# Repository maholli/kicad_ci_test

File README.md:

# kicad_ci_test

## maholli

Test for Continuous Integration using KiCad.

This is an example of how to test and generate documentation for a KiCad project automatically every time you commit a change to the schematic and/or PCB.

In this example we use a [docker image](https://github.com/INTI-CMNB/kicad_auto) containing KiCad, [KiPlot](https://github.com/INTI-CMNB/kiplot) and all the supporting tools.

The [kicad_ci_test.kiplot.yaml](https://github.com/INTI-CMNB/kicad_ci_test/blob/master/kicad_ci_test.kiplot.yaml) configures KiPlot and says what's available.

The [.github/workflows/test1.yml](https://github.com/INTI-CMNB/kicad_ci_test/blob/master/.github/workflows/test1.yml) configures what GitHub makes.

In this file we:

* Instruct GitHub to run the tasks every time a change in the pertinent files is detected:

```
on:
  push:
    branches: [ master ]
    paths:
      - '**.sch'
      - '**.kicad_pcb'
  pull_request:
    branches: [ master ]
    paths:
      - '**.sch'
      - '**.kicad_pcb'
```

* Define actions for ERC, DRC, schematic documentation generation and PCB documentation generation.
* Each action takes the repo content as input using:

```
- uses: actions/checkout@v2
```

* The actions are executed by KiPlot and stored in the *Fabrication* directory

* The resulting files are stored as *artifacts* using:

```
 - name: Recuperar resultados
      uses: actions/upload-artifact@v1
      with:
        name: ERC_Output
        path: Fabrication
```

For more information about the GitHub configuration read the [Workflow syntax for GitHub Actions](https://help.github.com/en/actions/reference/workflow-syntax-for-github-actions) page.

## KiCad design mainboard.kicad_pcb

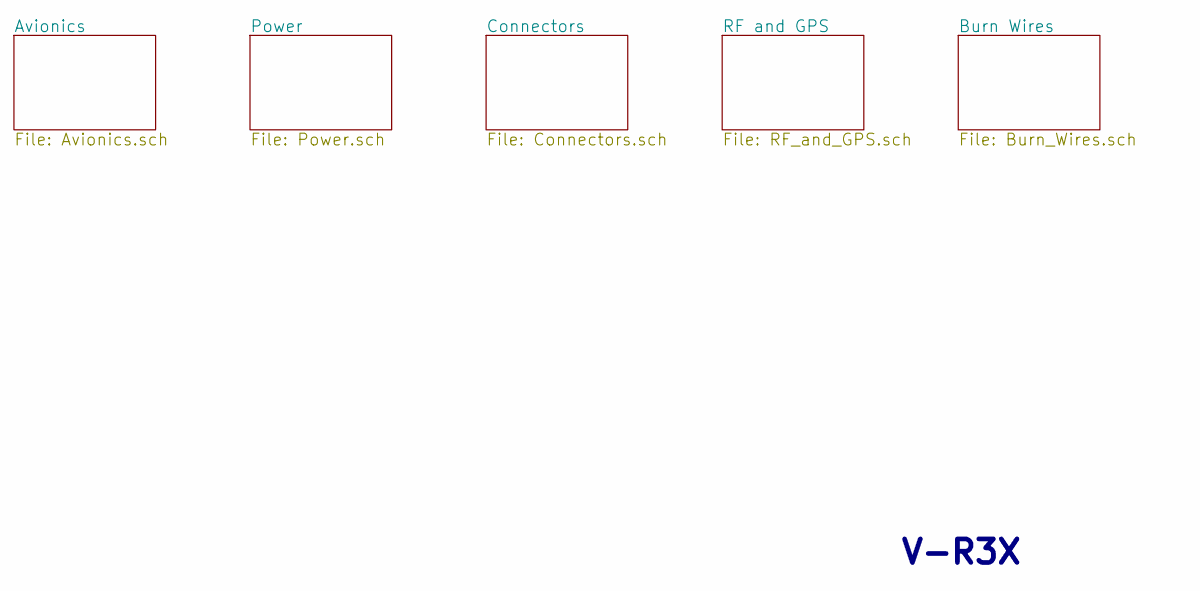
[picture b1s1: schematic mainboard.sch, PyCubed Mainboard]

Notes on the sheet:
V-R3X

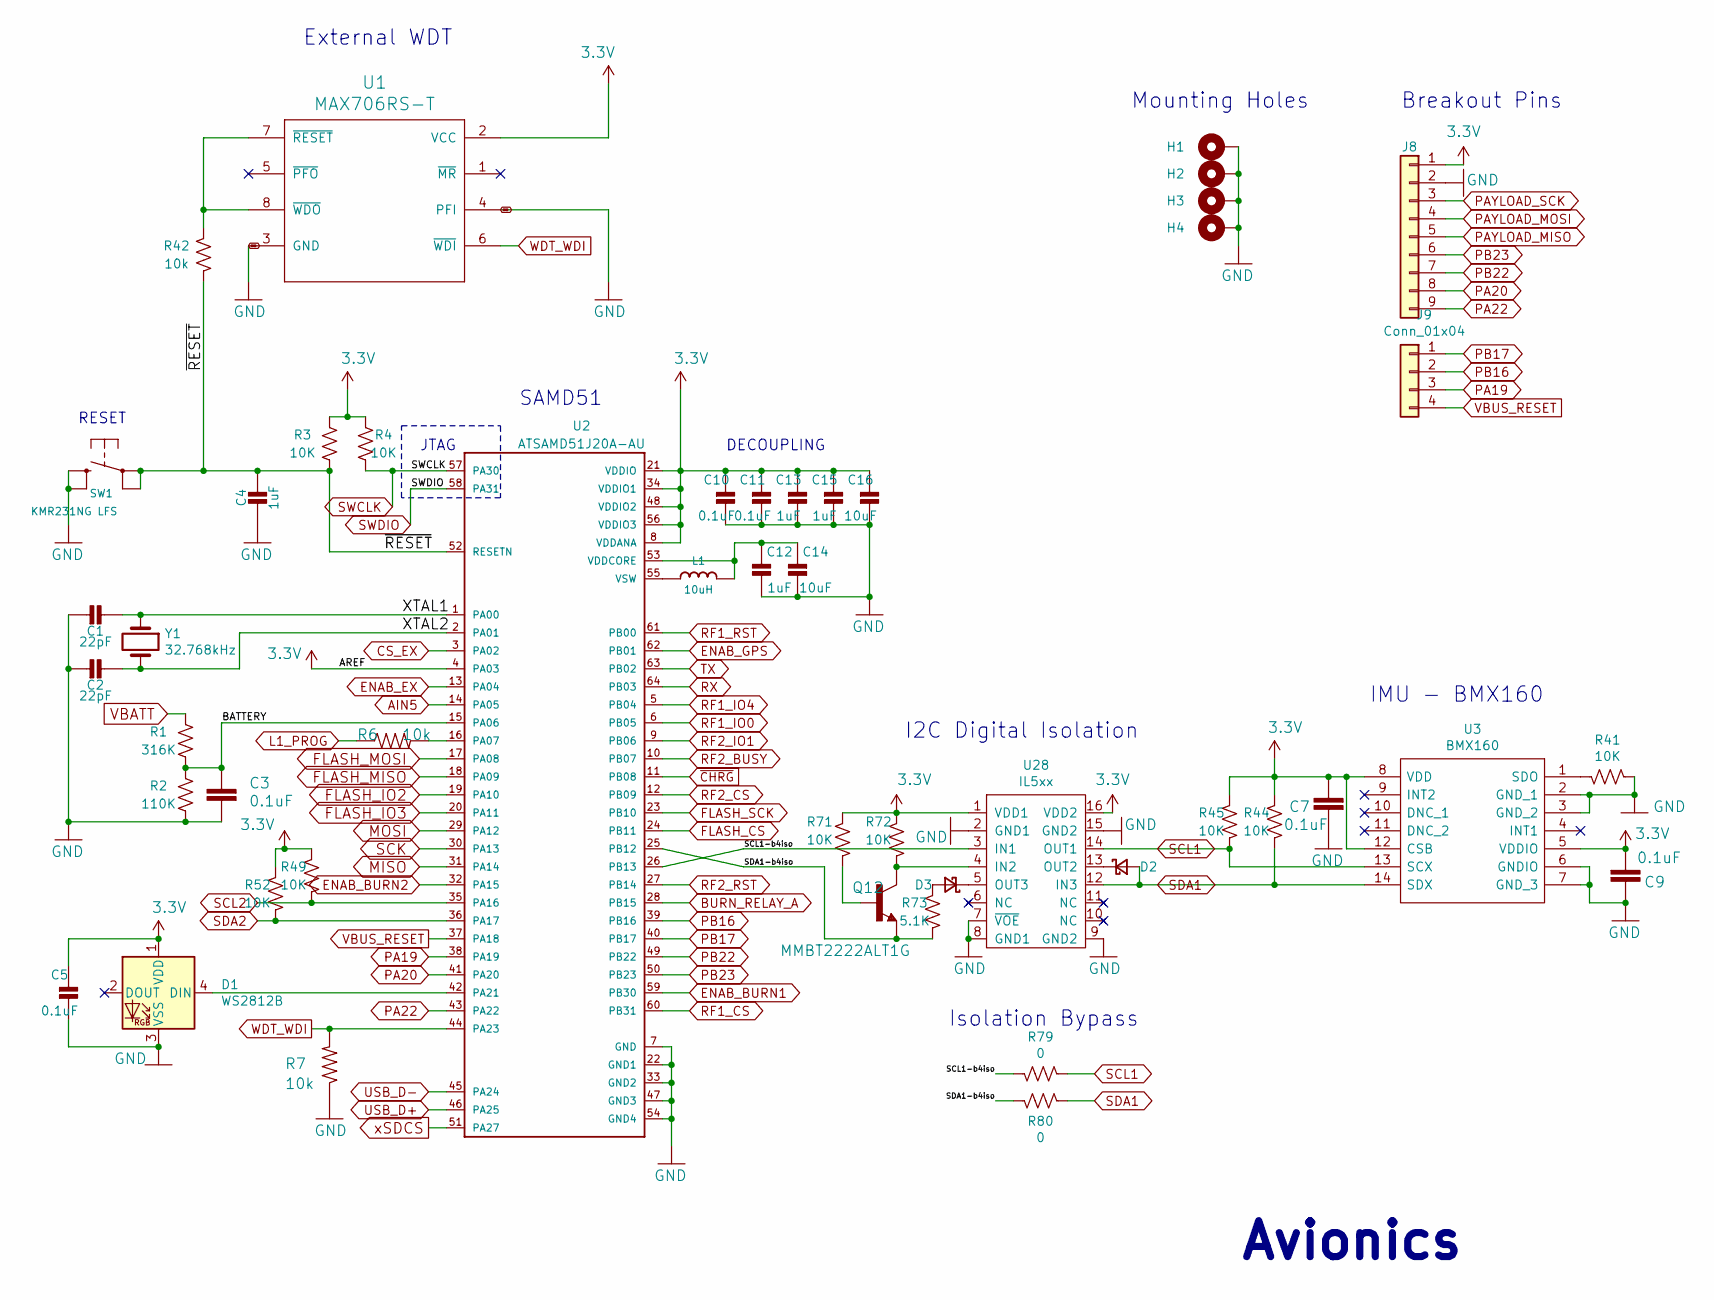
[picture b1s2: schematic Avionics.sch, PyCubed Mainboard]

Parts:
C1, C2: 22pF; C_0603_1608Metric
C3, C5, C7, C9, C10, C11: 0.1uF; C_0603_1608Metric
C4, C12, C13, C15: 1uF; C_0603_1608Metric
C14, C16: 10uF; C_0603_1608Metric
D1: WS2812B; LED_WS2812B_PLCC4_5.0x5.0mm_P3.2mm
D2, D3: RB550VAM; SOD-323HE
H1, H2, H3, H4: MountingHole_Pad; MountingHole_3.2mm_M3_DIN965_Pad
J8: Conn_01x09; PinHeader_1x09_P2.54mm_Vertical
J9: Conn_01x04; PinHeader_1x04_P2.54mm_Vertical
L1: 10uH; L_0805_2012Metric_Pad1.15x1.40mm_HandSolder
Q12: MMBT2222ALT1G; SOT23
R1: 316K; R_0603_1608Metric
R2: 110K; R_0603_1608Metric
R3, R4, R41, R44, R45, R49, R52, R71, R72: 10K; R_0603_1608Metric
R6, R7, R42: 10k; R_0603_1608Metric
R73: 5.1K; R_0603_1608Metric
R79, R80: 0; R_0603_1608Metric
SW1: KMR231NG LFS; BTN_KMR2_4.6X2.8
U1: MAX706RS-T; SO-8_3.9x4.9mm_P1.27mm
U2: ATSAMD51J20A-AU; QFP50P1200X1200X120-64N
U3: BMX160; Manufacturer_Part_Number BMX160; Mouser Part Number 262-BMX160
U28: IL5xx; SOIC-16_IL5xx
Y1: 32.768kHz; Crystal_SMD_3215-2Pin_3.2x1.5mm

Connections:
3.3V: C5.1, C7.1, C9.2, C10.1, C11.1, C13.1, C15.1, C16.1, D1.1 (VDD), J8.1, R3.1, R4.1, R44.1, R45.1, R49.1, R52.1, R71.2, R72.1, U1.2 (VCC), U2.4 (PA03), U2.8 (VDDANA), U2.21 (VDDIO), U2.34 (VDDIO1), U2.48 (VDDIO2), U2.56 (VDDIO3), U3.5 (VDDIO), U3.8 (VDD), U3.12 (CSB), U28.1 (VDD1), U28.16 (VDD2); also elsewhere on the board
/Avionics/BATTERY: C3.1, R1.2, R2.2, U2.15 (PA06)
/Avionics/SCL1-b4iso: R79.1, U2.26 (PB13), U28.3 (IN1)
/Avionics/SDA1-b4iso: Q12.2 (E), R73.2, R80.1, U2.25 (PB12)
/Avionics/XTAL1: C1.1, U2.1 (PA00), Y1.1
/Avionics/XTAL2: C2.1, U2.2 (PA01), Y1.2
/Avionics/~RESET: C4.2, R3.2, R42.1, SW1.A, SW1.A' (P1), U2.52 (RESETN)
AIN5: U2.14 (PA05); also elsewhere on the board
BURN_RELAY_A: U2.28 (PB15); also elsewhere on the board
CS_EX: U2.3 (PA02); also elsewhere on the board
ENAB_BURN1: U2.59 (PB30); also elsewhere on the board
ENAB_BURN2: U2.32 (PA15); also elsewhere on the board
ENAB_EX: U2.13 (PA04); also elsewhere on the board
ENAB_GPS: U2.62 (PB01); also elsewhere on the board
FLASH_CS: U2.24 (PB11); also elsewhere on the board
FLASH_IO2: U2.19 (PA10); also elsewhere on the board
FLASH_IO3: U2.20 (PA11); also elsewhere on the board
FLASH_MISO: U2.18 (PA09); also elsewhere on the board
FLASH_MOSI: U2.17 (PA08); also elsewhere on the board
FLASH_SCK: U2.23 (PB10); also elsewhere on the board
GND: C1.2, C2.2, C3.2, C4.1, C5.2, C7.2, C9.1, C10.2, C11.2, C12.1, C13.2, C14.2, C15.2, C16.2, D1.3 (VSS), H1.1, H2.1, H3.1, H4.1, J8.2, R2.1, R7.1, R41.1, SW1.B (S), SW1.B' (S1), U1.3 (GND), U1.4 (PFI), U2.7 (GND), U2.22 (GND1), U2.33 (GND2), U2.47 (GND3), U2.54 (GND4), U3.2 (GND_1), U3.3 (GND_2), U3.6 (GNDIO), U3.7 (GND_3), U28.2 (GND1), U28.7 (~VOE), U28.8 (GND1), U28.9 (GND2), U28.15 (GND2); also elsewhere on the board
L1_PROG: R6.1; also elsewhere on the board
MISO: U2.31 (PA14); also elsewhere on the board
MOSI: U2.29 (PA12); also elsewhere on the board
unnamed: C12.2, C14.1, L1.1, U2.53 (VDDCORE)
unnamed: D1.4 (DIN), U2.42 (PA21)
unnamed: D2.1 (K), U28.13 (OUT2)
unnamed: D3.1 (K), U28.5 (OUT3)
unnamed: D3.2 (A), R73.1
unnamed: L1.2, U2.55 (VSW)
unnamed: Q12.1 (B), R71.1
unnamed: Q12.3 (C), R72.2, U28.4 (IN2)
unnamed: R6.2, U2.16 (PA07)
unnamed: R41.2, U3.1 (SDO)
unnamed: R42.2, U1.7 (~RESET), U1.8 (~WDO)
PA19: J9.3, U2.38 (PA19); also elsewhere on the board
PA20: J8.8, U2.41 (PA20); also elsewhere on the board
PA22: J8.9, U2.43 (PA22); also elsewhere on the board
PAYLOAD_MISO: J8.5; also elsewhere on the board
PAYLOAD_MOSI: J8.4; also elsewhere on the board
PAYLOAD_SCK: J8.3; also elsewhere on the board
PB16: J9.2, U2.39 (PB16); also elsewhere on the board
PB17: J9.1, U2.40 (PB17); also elsewhere on the board
PB22: J8.7, U2.49 (PB22); also elsewhere on the board
PB23: J8.6, U2.50 (PB23); also elsewhere on the board
RF1_CS: U2.60 (PB31); also elsewhere on the board
RF1_IO0: U2.6 (PB05); also elsewhere on the board
RF1_IO4: U2.5 (PB04); also elsewhere on the board
RF1_RST: U2.61 (PB00); also elsewhere on the board
RF2_BUSY: U2.10 (PB07); also elsewhere on the board
RF2_CS: U2.12 (PB09); also elsewhere on the board
RF2_IO1: U2.9 (PB06); also elsewhere on the board
RF2_RST: U2.27 (PB14); also elsewhere on the board
RX: U2.64 (PB03); also elsewhere on the board
SCK: U2.30 (PA13); also elsewhere on the board
SCL1: R45.2, R79.2, U3.13 (SCX), U28.14 (OUT1); also elsewhere on the board
SCL2: R49.2, U2.35 (PA16); also elsewhere on the board
SDA1: D2.2 (A), R44.2, R80.2, U3.14 (SDX), U28.12 (IN3); also elsewhere on the board
SDA2: R52.2, U2.36 (PA17); also elsewhere on the board
SWCLK: R4.2, U2.57 (PA30); also elsewhere on the board
SWDIO: U2.58 (PA31); also elsewhere on the board
TX: U2.63 (PB02); also elsewhere on the board
USB_D+: U2.46 (PA25); also elsewhere on the board
USB_D-: U2.45 (PA24); also elsewhere on the board
VBATT: R1.1; also elsewhere on the board
VBUS_RESET: J9.4, U2.37 (PA18); also elsewhere on the board
WDT_WDI: R7.2, U1.6 (~WDI), U2.44 (PA23)
xSDCS: U2.51 (PA27); also elsewhere on the board
~CHRG: U2.11 (PB08); also elsewhere on the board

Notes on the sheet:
RESET
External WDT
JTAG
SAMD51
DECOUPLING
Mounting Holes
I2C Digital Isolation
Isolation Bypass
Avionics
Breakout Pins
IMU - BMX160

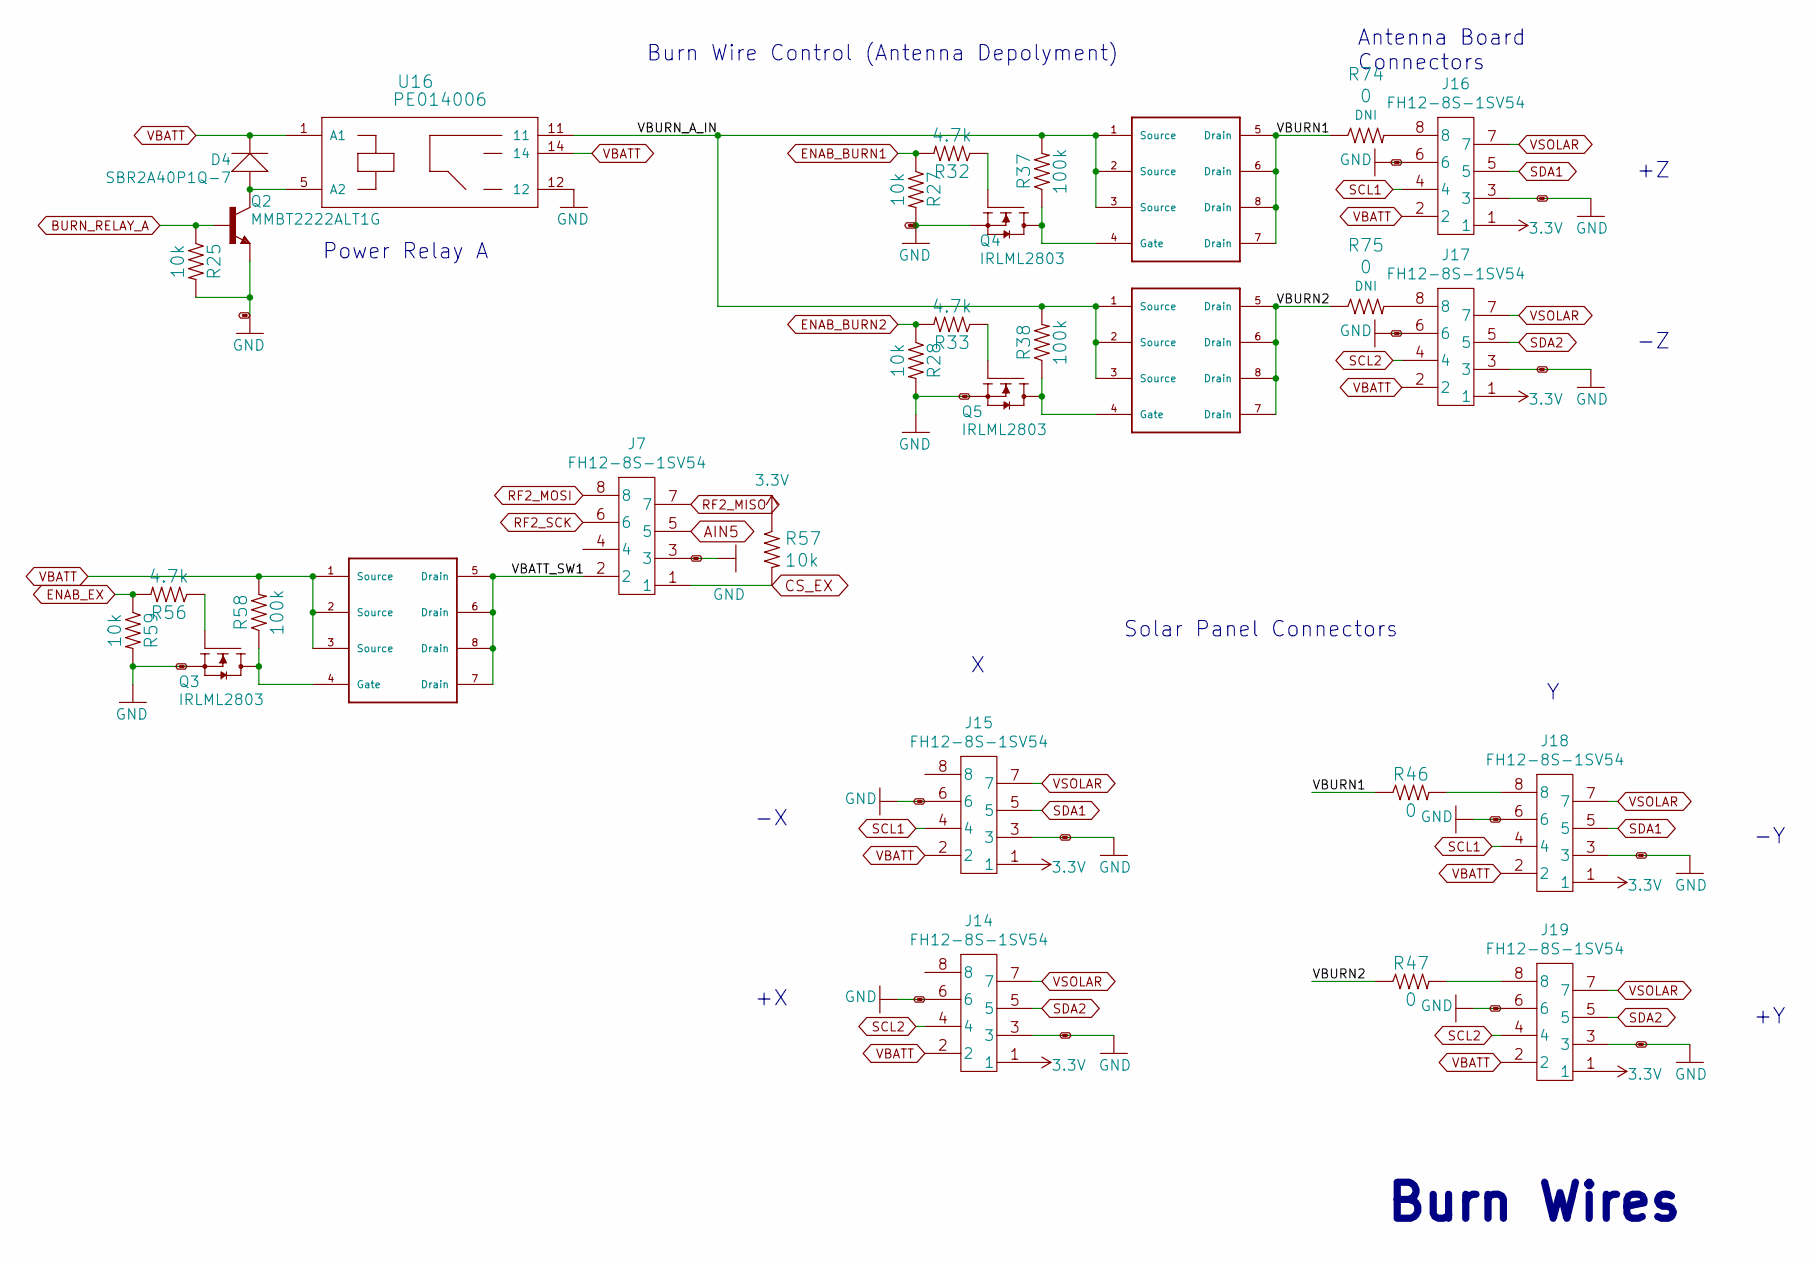
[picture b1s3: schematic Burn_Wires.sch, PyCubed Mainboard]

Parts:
D4: SBR2A40P1Q-7; PWRDI-123
J7, J14, J15, J16, J17, J18, J19: FH12-8S-1SV54; FH12-8S-1SV
Q2: MMBT2222ALT1G; SOT23
Q3, Q4, Q5: IRLML2803; SOT-23
R25, R27, R28, R57, R59: 10k; R_0603_1608Metric
R32, R33, R56: 4.7k; R_0603_1608Metric
R37, R38, R58: 100k; R_0603_1608Metric
R46, R47, R74, R75: 0; R_0603_1608Metric
U16: PE014006; RELAY5-PE_CO
U18, U19, U22: NDS8434

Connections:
3.3V: J14.1, J15.1, J16.1, J17.1, J18.1, J19.1, R57.1; also elsewhere on the board
/Burn Wires/VBATT_SW1: J7.2, U22.5 (Drain), U22.6 (Drain), U22.7 (Drain), U22.8 (Drain)
/Burn Wires/VBURN1: R46.1, R74.1, U18.5 (Drain), U18.6 (Drain), U18.7 (Drain), U18.8 (Drain)
/Burn Wires/VBURN2: R47.1, R75.1, U19.5 (Drain), U19.6 (Drain), U19.7 (Drain), U19.8 (Drain)
/Burn Wires/VBURN_A_IN: R37.2, R38.2, U16.11, U18.1 (Source), U18.2 (Source), U18.3 (Source), U19.1 (Source), U19.2 (Source), U19.3 (Source)
AIN5: J7.5; also elsewhere on the board
BURN_RELAY_A: Q2.1 (B), R25.1; also elsewhere on the board
CS_EX: J7.1, R57.2; also elsewhere on the board
ENAB_BURN1: R27.1, R32.2; also elsewhere on the board
ENAB_BURN2: R28.1, R33.2; also elsewhere on the board
ENAB_EX: R56.2, R59.1; also elsewhere on the board
GND: J7.3, J14.3, J14.6, J15.3, J15.6, J16.3, J16.6, J17.3, J17.6, J18.3, J18.6, J19.3, J19.6, Q2.2 (E), Q3.2 (S), Q4.2 (S), Q5.2 (S), R25.2, R27.2, R28.2, R59.2, U16.12; also elsewhere on the board
unnamed: D4.A, Q2.3 (C), U16.5 (A2)
unnamed: J16.8, R74.2
unnamed: J17.8, R75.2
unnamed: J18.8, R46.2
unnamed: J19.8, R47.2
unnamed: Q3.1 (G), R56.1
unnamed: Q3.3 (D), R58.1, U22.4 (Gate)
unnamed: Q4.1 (G), R32.1
unnamed: Q4.3 (D), R37.1, U18.4 (Gate)
unnamed: Q5.1 (G), R33.1
unnamed: Q5.3 (D), R38.1, U19.4 (Gate)
RF2_MISO: J7.7; also elsewhere on the board
RF2_MOSI: J7.8; also elsewhere on the board
RF2_SCK: J7.6; also elsewhere on the board
SCL1: J15.4, J16.4, J18.4; also elsewhere on the board
SCL2: J14.4, J17.4, J19.4; also elsewhere on the board
SDA1: J15.5, J16.5, J18.5; also elsewhere on the board
SDA2: J14.5, J17.5, J19.5; also elsewhere on the board
VBATT: D4.C, J14.2, J15.2, J16.2, J17.2, J18.2, J19.2, R58.2, U16.1 (A1), U16.14, U22.1 (Source), U22.2 (Source), U22.3 (Source); also elsewhere on the board
VSOLAR: J14.7, J15.7, J16.7, J17.7, J18.7, J19.7; also elsewhere on the board

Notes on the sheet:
Power Relay A
Burn Wire Control (Antenna Depolyment)
Solar Panel Connectors
Antenna Board Connectors
Burn Wires

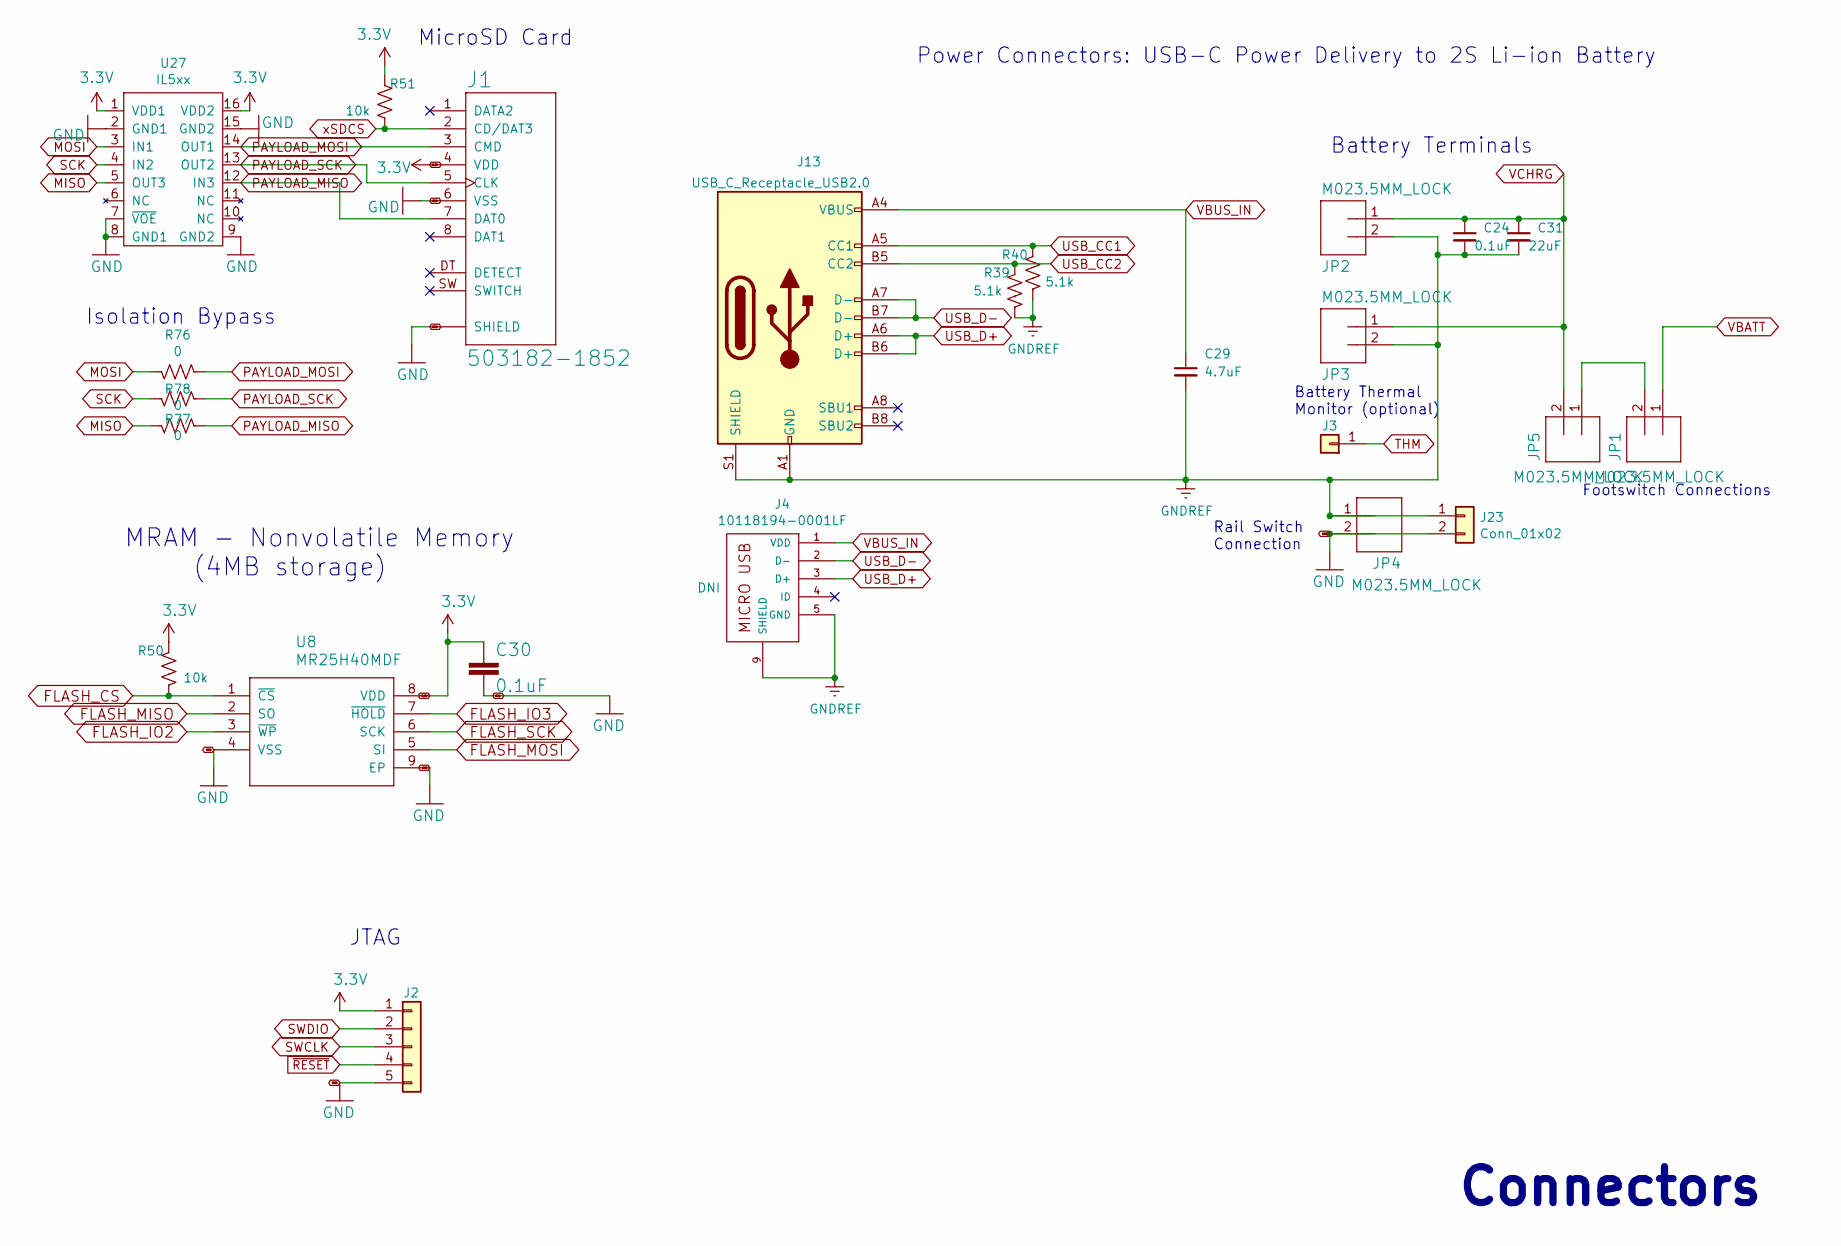
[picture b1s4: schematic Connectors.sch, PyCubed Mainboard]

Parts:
C24, C30: 0.1uF; C_0603_1608Metric
C29: 4.7uF; C_0603_1608Metric
C31: 22uF; C_0603_1608Metric
J1: 503182-1852; MOLEX_503182-1852
J2: Conn_01x05; PinHeader_1x05_P2.54mm_Vertical
J3: Conn_01x01; PinHeader_1x01_P2.54mm_Vertical
J4: 10118194-0001LF
J13: USB_C_Receptacle_USB2.0; USB_C_Receptacle_XKB_U262-161N-4BVC11
J23: Conn_01x02; PinHeader_1x02_P2.54mm_Vertical_SLIM
JP1, JP2, JP3, JP4, JP5: M023.5MM_LOCK; SCREWTERMINAL-3.5MM-2_LOCK
R39, R40: 5.1k; R_0603_1608Metric
R50, R51: 10k; R_0603_1608Metric
R76, R77, R78: 0; R_0603_1608Metric
U8: MR25H40MDF; SON127P600X500X90-9N
U27: IL5xx; SOIC-16_IL5xx

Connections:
3.3V: C30.1, J1.4 (VDD), J2.1, R50.2, R51.2, U8.8 (VDD), U27.1 (VDD1), U27.16 (VDD2); also elsewhere on the board
FLASH_CS: R50.1, U8.1 (~CS); also elsewhere on the board
FLASH_IO2: U8.3 (~WP); also elsewhere on the board
FLASH_IO3: U8.7 (~HOLD); also elsewhere on the board
FLASH_MISO: U8.2 (SO); also elsewhere on the board
FLASH_MOSI: U8.5 (SI); also elsewhere on the board
FLASH_SCK: U8.6 (SCK); also elsewhere on the board
GND: C30.2, J1.6 (VSS), J1.P1 (SHIELD), J1.P2 (SHIELD), J1.P3 (SHIELD), J1.P4 (SHIELD), J1.P5 (SHIELD), J2.5, J23.2, JP4.2, U8.4 (VSS), U8.9 (EP), U27.2 (GND1), U27.7 (~VOE), U27.8 (GND1), U27.9 (GND2), U27.15 (GND2); also elsewhere on the board
GNDREF: C24.2, C29.2, C31.2, J4.5 (GND), J4.8, J4.9 (SHIELD), J13.A1 (GND), J13.A12 (GND), J13.B1 (GND), J13.B12 (GND), J13.S1 (SHIELD), J23.1, JP2.2, JP3.2, JP4.1, R39.1, R40.1; also elsewhere on the board
MISO: R78.1, U27.5 (OUT3); also elsewhere on the board
MOSI: R76.1, U27.3 (IN1); also elsewhere on the board
unnamed: JP1.2, JP5.1
PAYLOAD_MISO: J1.7 (DAT0), R78.2, U27.12 (IN3); also elsewhere on the board
PAYLOAD_MOSI: J1.3 (CMD), R76.2, U27.14 (OUT1); also elsewhere on the board
PAYLOAD_SCK: J1.5 (CLK), R77.2, U27.13 (OUT2); also elsewhere on the board
SCK: R77.1, U27.4 (IN2); also elsewhere on the board
SWCLK: J2.3; also elsewhere on the board
SWDIO: J2.2; also elsewhere on the board
THM: J3.1; also elsewhere on the board
USB_CC1: J13.A5 (CC1), R40.2
USB_CC2: J13.B5 (CC2), R39.2
USB_D+: J4.3 (D+), J13.A6 (D+), J13.B6 (D+); also elsewhere on the board
USB_D-: J4.2 (D-), J13.A7 (D-), J13.B7 (D-); also elsewhere on the board
VBATT: JP1.1; also elsewhere on the board
VBUS_IN: C29.1, J4.1 (VDD), J13.A4 (VBUS), J13.A9 (VBUS), J13.B4 (VBUS), J13.B9 (VBUS); also elsewhere on the board
VCHRG: C24.1, C31.1, JP2.1, JP3.1, JP5.2; also elsewhere on the board
xSDCS: J1.2 (CD/DAT3), R51.1; also elsewhere on the board
~RESET: J2.4

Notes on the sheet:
MRAM - Nonvolatile Memory (4MB storage)
Isolation Bypass
JTAG
MicroSD Card
Power Connectors: USB-C Power Delivery to 2S Li-ion Battery
Rail Switch Connection
Battery Thermal Monitor (optional)
Battery Terminals
Connectors
Footswitch Connections

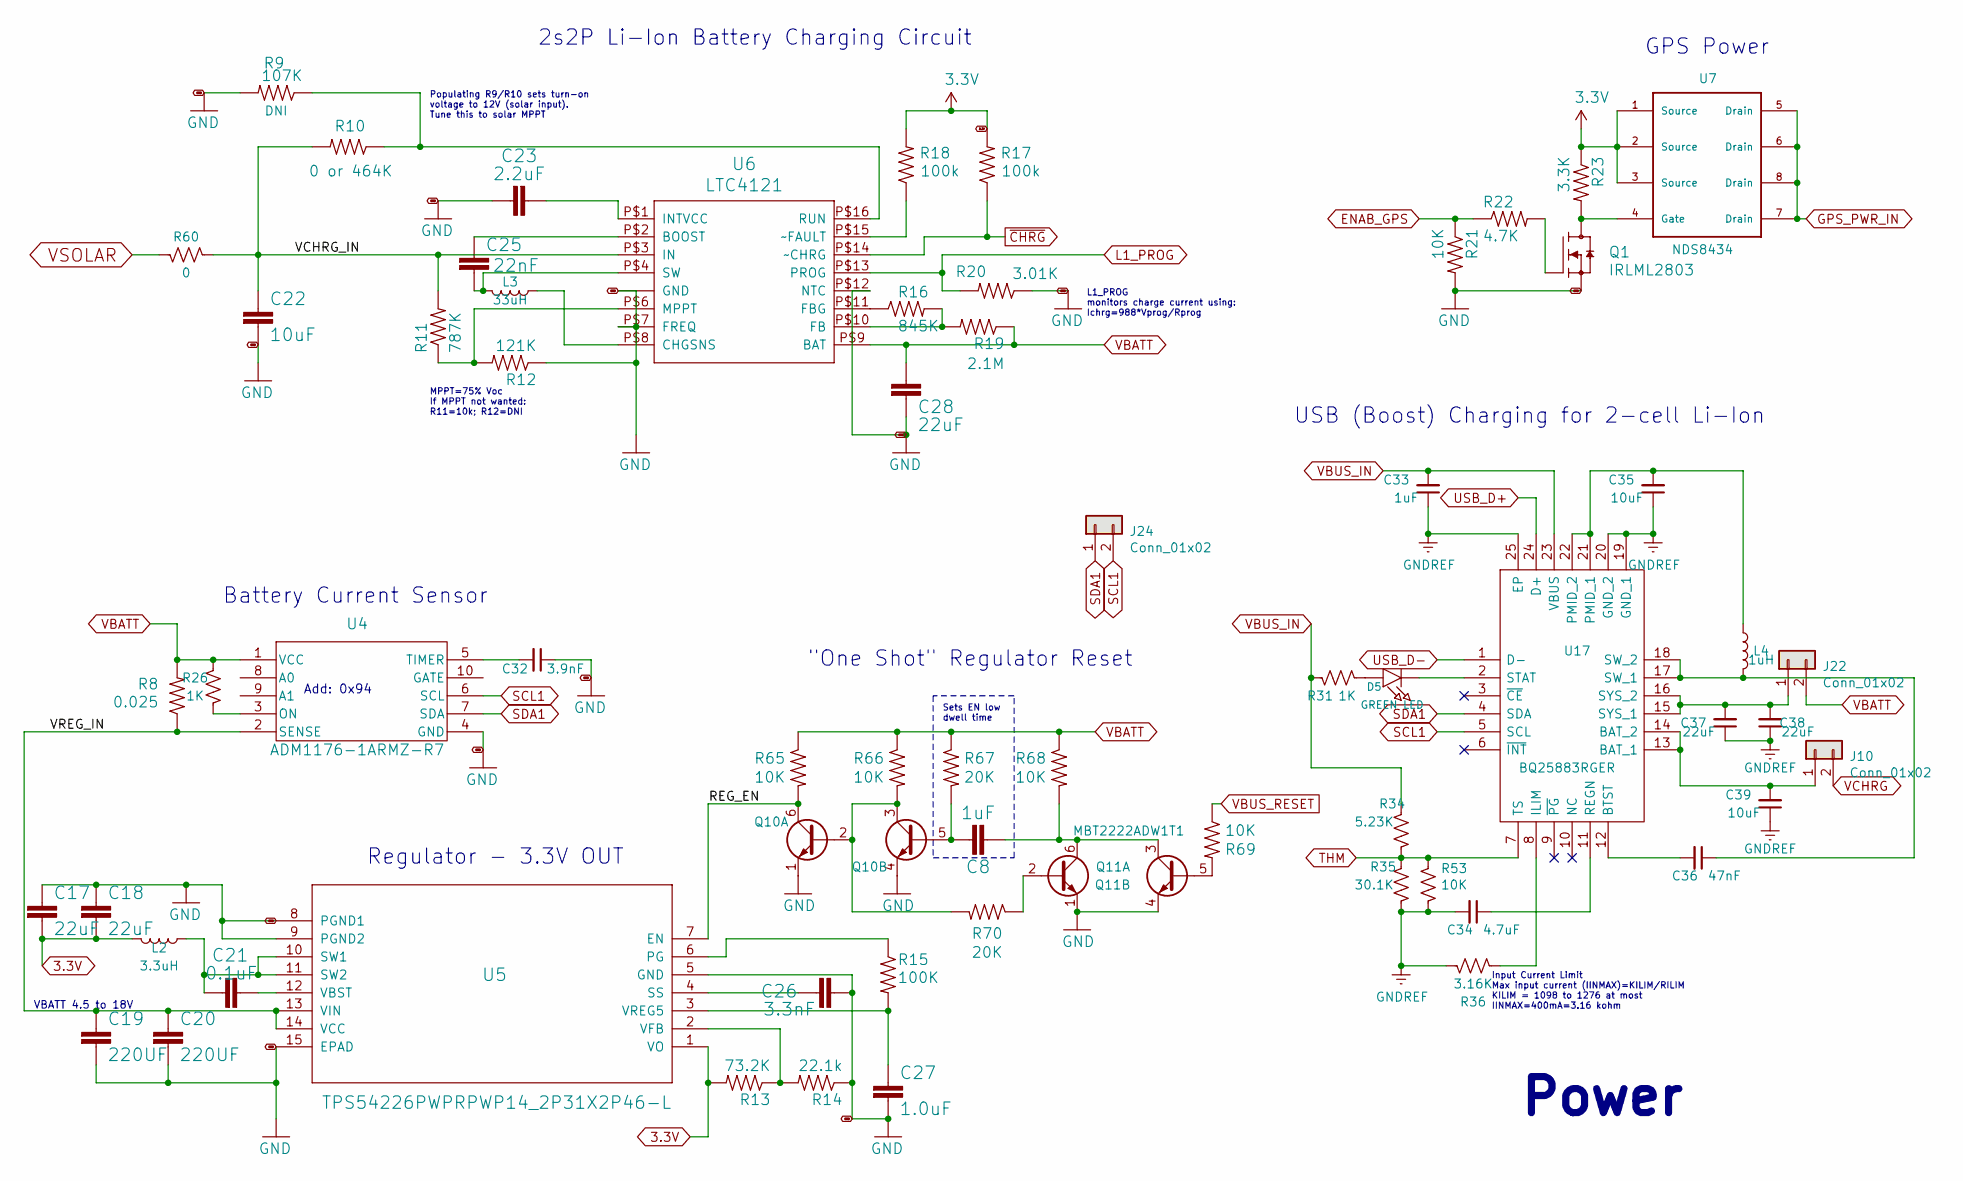
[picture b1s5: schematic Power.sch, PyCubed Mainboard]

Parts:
C8, C33: 1uF; C_0603_1608Metric
C17, C18, C28, C37, C38: 22uF; C_0603_1608Metric
C19, C20: 220UF; C_1210_3225Metric
C21: 0.1uF; C_0603_1608Metric
C22, C35, C39: 10uF; C_0603_1608Metric
C23: 2.2uF; C_0603_1608Metric
C25: 22nF; C_0603_1608Metric
C26: 3.3nF; C_0603_1608Metric
C27: 1.0uF; C_0603_1608Metric
C32: 3.9nF; C_0603_1608Metric
C34: 4.7uF; C_0603_1608Metric
C36: 47nF; C_0603_1608Metric
D5: GREEN LED; LED_0603_1608Metric
J10, J22, J24: Conn_01x02; PinHeader_1x02_P2.54mm_Vertical_SLIM
L2: 3.3uH; L_2141
L3: 33uH; L_1812_4532Metric
L4: 1uH; XFL4030472MEB
Q1: IRLML2803; SOT-23
Q10, Q11: MBT2222ADW1T1; SOT-363_SC-70-6
R8: 0.025; R_2512_6332Metric
R9: 107K; R_0603_1608Metric
R10: 0 or 464K; R_0603_1608Metric
R11: 787K; R_0603_1608Metric
R12: 121K; R_0603_1608Metric
R13: 73.2K; R_0603_1608Metric
R14: 22.1k; R_0603_1608Metric
R15: 100K; R_0603_1608Metric
R16: 845K; R_0603_1608Metric
R17, R18: 100k; R_0603_1608Metric
R19: 2.1M; R_0603_1608Metric
R20: 3.01K; R_0603_1608Metric
R21, R53, R65, R66, R68, R69: 10K; R_0603_1608Metric
R22: 4.7K; R_0603_1608Metric
R23: 3.3K; R_0603_1608Metric
R26, R31: 1K; R_0603_1608Metric
R34: 5.23K; R_0603_1608Metric
R35: 30.1K; R_0603_1608Metric
R36: 3.16K; R_0603_1608Metric
R60: 0; R_0805_2012Metric
R67, R70: 20K; R_0603_1608Metric
U4: ADM1176-1ARMZ-R7
U5: TPS54226PWPRPWP14_2P31X2P46-L; PWP14_2P31X2P46-L
U6: LTC4121; QFN-16-PAD
U7: NDS8434
U17: BQ25883RGER; QFN50P400X400X100-25N-D; Manufacturer_Part_Number BQ25883RGER; Mouser Part Number 595-BQ25883RGER

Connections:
3.3V: C17.2, C18.2, L2.2, R13.2, R17.2, R18.2, R23.1, U5.1 (VO), U7.1 (Source), U7.2 (Source), U7.3 (Source); also elsewhere on the board
/Power/REG_EN: Q10.6 (C1), R65.2, U5.7 (EN)
/Power/VCHRG_IN: C22.1, R10.2, R11.2, R60.1, U6.P$3 (IN)
/Power/VREG_IN: C19.1, C20.1, R8.1, U4.2 (SENSE), U5.13 (VIN), U5.14 (VCC)
ENAB_GPS: R21.1, R22.1; also elsewhere on the board
GND: C17.1, C18.1, C19.2, C20.2, C22.2, C23.2, C26.2, C27.2, C28.2, C32.1, Q1.2 (S), Q10.1 (E1), Q10.4 (E2), Q11.1 (E1), Q11.4 (E2), R9.2, R12.1, R14.1, R20.1, R21.2, U4.4 (GND), U5.5 (GND), U5.8 (PGND1), U5.9 (PGND2), U5.15 (EPAD), U6.P$5 (GND), U6.P$7 (FREQ), U6.P$12 (NTC), U6.P$17 (GND); also elsewhere on the board
GNDREF: C33.1, C34.2, C35.1, C37.1, C38.1, C39.1, R35.1, R36.1, R53.2, U17.19 (GND_1), U17.20 (GND_2), U17.25 (EP); also elsewhere on the board
GPS_PWR_IN: U7.5 (Drain), U7.6 (Drain), U7.7 (Drain), U7.8 (Drain); also elsewhere on the board
L1_PROG: R20.2, U6.P$13 (PROG); also elsewhere on the board
unnamed: C8.1, Q10.5 (B2), R67.2
unnamed: C8.2, Q11.3 (C2), Q11.6 (C1), R68.2
unnamed: C21.1, L2.1, U5.10 (SW1), U5.11 (SW2)
unnamed: C21.2, U5.12 (VBST)
unnamed: C23.1, U6.P$1 (INTVCC)
unnamed: C25.1, U6.P$2 (BOOST)
unnamed: C25.2, L3.2, U6.P$4 (SW)
unnamed: C26.1, U5.4 (SS)
unnamed: C27.1, R15.2, U5.3 (VREG5)
unnamed: C32.2, U4.5 (TIMER)
unnamed: C34.1, U17.11 (REGN)
unnamed: C35.2, L4.1, U17.21 (PMID_1), U17.22 (PMID_2)
unnamed: C36.1, L4.2, U17.17 (SW_1), U17.18 (SW_2)
unnamed: C36.2, U17.12 (BTST)
unnamed: C37.2, C38.2, J22.1, U17.15 (SYS_1), U17.16 (SYS_2)
unnamed: C39.2, J10.1, U17.13 (BAT_1), U17.14 (BAT_2)
unnamed: D5.1, R31.1
unnamed: D5.2, U17.2 (STAT)
unnamed: L3.1, U6.P$8 (CHGSNS)
unnamed: Q1.1 (G), R22.2
unnamed: Q1.3 (D), R23.2, U7.4 (Gate)
unnamed: Q10.2 (B1), Q10.3 (C2), R66.2, R70.2
unnamed: Q11.2 (B1), R70.1
unnamed: Q11.5 (B2), R69.2
unnamed: R9.1, R10.1, U6.P$16 (RUN)
unnamed: R11.1, R12.2, U6.P$6 (MPPT)
unnamed: R13.1, R14.2, U5.2 (VFB)
unnamed: R15.1, U5.6 (PG)
unnamed: R16.1, U6.P$11 (FBG)
unnamed: R16.2, R19.2, U6.P$10 (FB)
unnamed: R18.1, U6.P$15 (~~FAULT)
unnamed: R26.1, U4.3 (ON)
unnamed: R36.2, U17.8 (ILIM)
SCL1: J24.2, U4.6 (SCL), U17.5 (SCL); also elsewhere on the board
SDA1: J24.1, U4.7 (SDA), U17.4 (SDA); also elsewhere on the board
THM: R34.2, R35.2, R53.1, U17.7 (TS); also elsewhere on the board
USB_D+: U17.24 (D+); also elsewhere on the board
USB_D-: U17.1 (D-); also elsewhere on the board
VBATT: C28.1, J22.2, R8.2, R19.1, R26.2, R65.1, R66.1, R67.1, R68.1, U4.1 (VCC), U6.P$9 (BAT); also elsewhere on the board
VBUS_IN: C33.2, R31.2, R34.1, U17.23 (VBUS); also elsewhere on the board
VBUS_RESET: R69.1; also elsewhere on the board
VCHRG: J10.2; also elsewhere on the board
VSOLAR: R60.2; also elsewhere on the board
~CHRG: R17.1, U6.P$14 (~~CHRG); also elsewhere on the board

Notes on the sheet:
VBATT 4.5 to 18V
Battery Current Sensor
Add: 0x94
Regulator - 3.3V OUT
Populating R9/R10 sets turn-on voltage to 12V (solar input). Tune this to solar MPPT
MPPT=75% Voc If MPPT not wanted: R11=10k; R12=DNI
2s2P Li-Ion Battery Charging Circuit
"One Shot" Regulator Reset
Sets EN low dwell time
L1_PROG monitors charge current using: Ichrg=988*Vprog/Rprog
USB (Boost) Charging for 2-cell Li-Ion
Input Current Limit Max input current (IINMAX)=KILIM/RILIM KILIM = 1098 to 1276 at most IINMAX=400mA=3.16 kohm
Power
GPS Power

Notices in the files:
parts and their libraries:
Copyright 2016 Accelerated Designs. All rights reserved.
